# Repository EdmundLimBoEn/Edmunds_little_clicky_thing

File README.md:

### Edmunds little clicky thing

### Description
A tiny little companion for my mac/desktop,
Multiple profiles using layers in VIAL (not sure of qmk configurator alternative), for different tasks like 3D modelling with easy-to-reach shortcuts for things requiring multiple keys to be pressed, a general layer with screenshot commands (my hands are small so mac screenshot is hard to reach), and other simple automations like keys to open different apps/automations. M

### Requirements
- QMK firmware (UF2)
- QMK configurator/VIAL (I am using VIAL)

### BOM

|No.|Quantity|Item|
|---|--------|----|
|1|16|1N4148 Diode|
|2|16|Cherry MX Switch|
|3|16|Keycap|
|4|1|Seeed Studio XIAO RP2040|
|5|1|Case Top (3d printed)|
|6|1|Case Bottom (3d printed)|
|7|4| M3 Screw|
|8|4| M3 Heatset insert|
|9|1|PCB|

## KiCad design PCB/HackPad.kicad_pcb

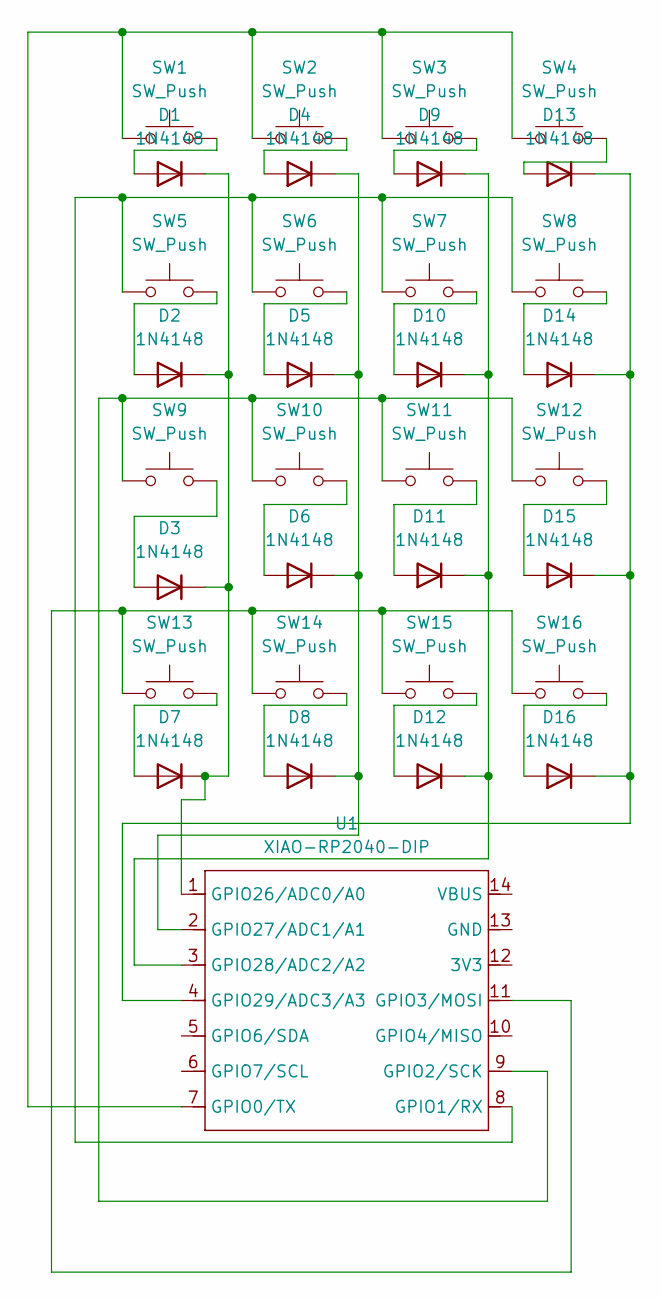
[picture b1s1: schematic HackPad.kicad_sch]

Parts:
D1, D2, D3, D4, D5, D6, D7, D8, D9, D10, D11, D12, D13, D14, D15, D16: 1N4148; D_DO-35_SOD27_P7.62mm_Horizontal
SW1, SW2, SW3, SW4, SW5, SW6, SW7, SW8, SW9, SW10, SW11, SW12, SW13, SW14, SW15, SW16: SW_Push; SW_Cherry_MX_1.00u_PCB
U1: XIAO-RP2040-DIP

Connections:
unnamed: D1.2 (A), SW1.2
unnamed: D1.1 (K), D2.1 (K), D3.1 (K), D7.1 (K), U1.1 (GPIO26/ADC0/A0)
unnamed: D2.2 (A), SW5.2
unnamed: D3.2 (A), SW9.2
unnamed: D4.2 (A), SW2.2
unnamed: D4.1 (K), D5.1 (K), D6.1 (K), D8.1 (K), U1.2 (GPIO27/ADC1/A1)
unnamed: D5.2 (A), SW6.2
unnamed: D6.2 (A), SW10.2
unnamed: D7.2 (A), SW13.2
unnamed: D8.2 (A), SW14.2
unnamed: D9.2 (A), SW3.2
unnamed: D10.2 (A), SW7.2
unnamed: D9.1 (K), D10.1 (K), D11.1 (K), D12.1 (K), U1.3 (GPIO28/ADC2/A2)
unnamed: D11.2 (A), SW11.2
unnamed: D12.2 (A), SW15.2
unnamed: D13.2 (A), SW4.2
unnamed: D13.1 (K), D14.1 (K), D15.1 (K), D16.1 (K), U1.4 (GPIO29/ADC3/A3)
unnamed: D14.2 (A), SW8.2
unnamed: D15.2 (A), SW12.2
unnamed: D16.2 (A), SW16.2
unnamed: SW1.1, SW2.1, SW3.1, SW4.1, U1.7 (GPIO0/TX)
unnamed: SW5.1, SW6.1, SW7.1, SW8.1, U1.8 (GPIO1/RX)
unnamed: SW9.1, SW10.1, SW11.1, SW12.1, U1.9 (GPIO2/SCK)
unnamed: SW13.1, SW14.1, SW15.1, SW16.1, U1.11 (GPIO3/MOSI)

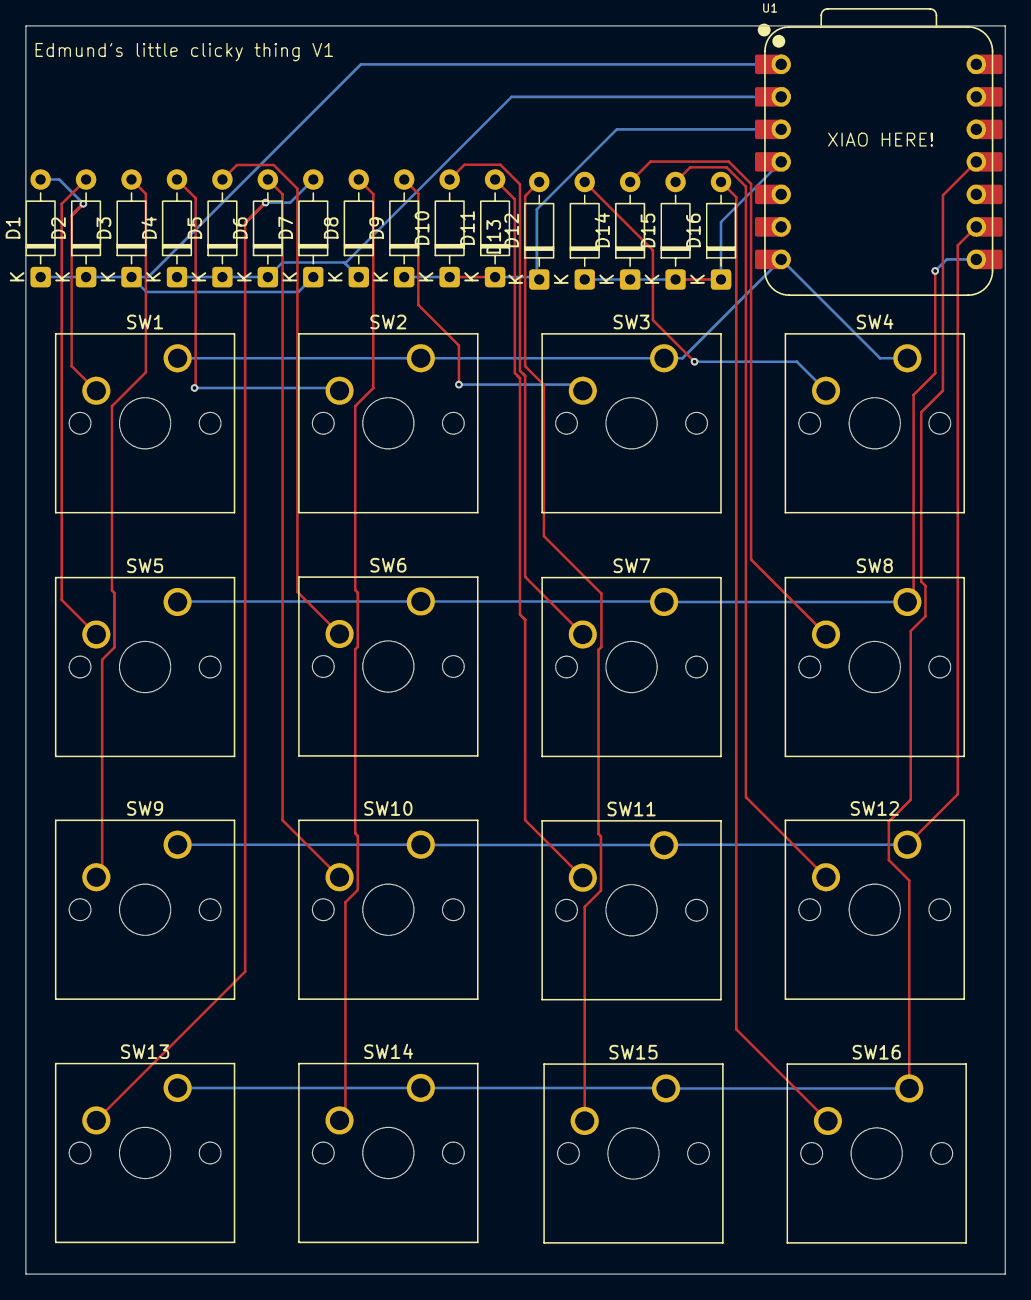
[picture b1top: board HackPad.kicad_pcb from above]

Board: 2 copper layers, 76.5 x 97.5 mm, 33 parts (0 on the bottom side), 24 nets.

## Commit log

2025-11-30 Add README content for Edmund's clicky thing
    Added specifications and images for Edmund's clicky thing.
2025-11-30 added cad, pcb and firmware
2025-12-01 added UF2 firmware
2025-12-03 Revise README with description and requirements
    Updated the README to include a description and requirements section, and formatted the BOM into a table.
2025-12-03 added missing BOM title
    oopsies
2025-12-03 added bom css
    idk what im doing pelase help
